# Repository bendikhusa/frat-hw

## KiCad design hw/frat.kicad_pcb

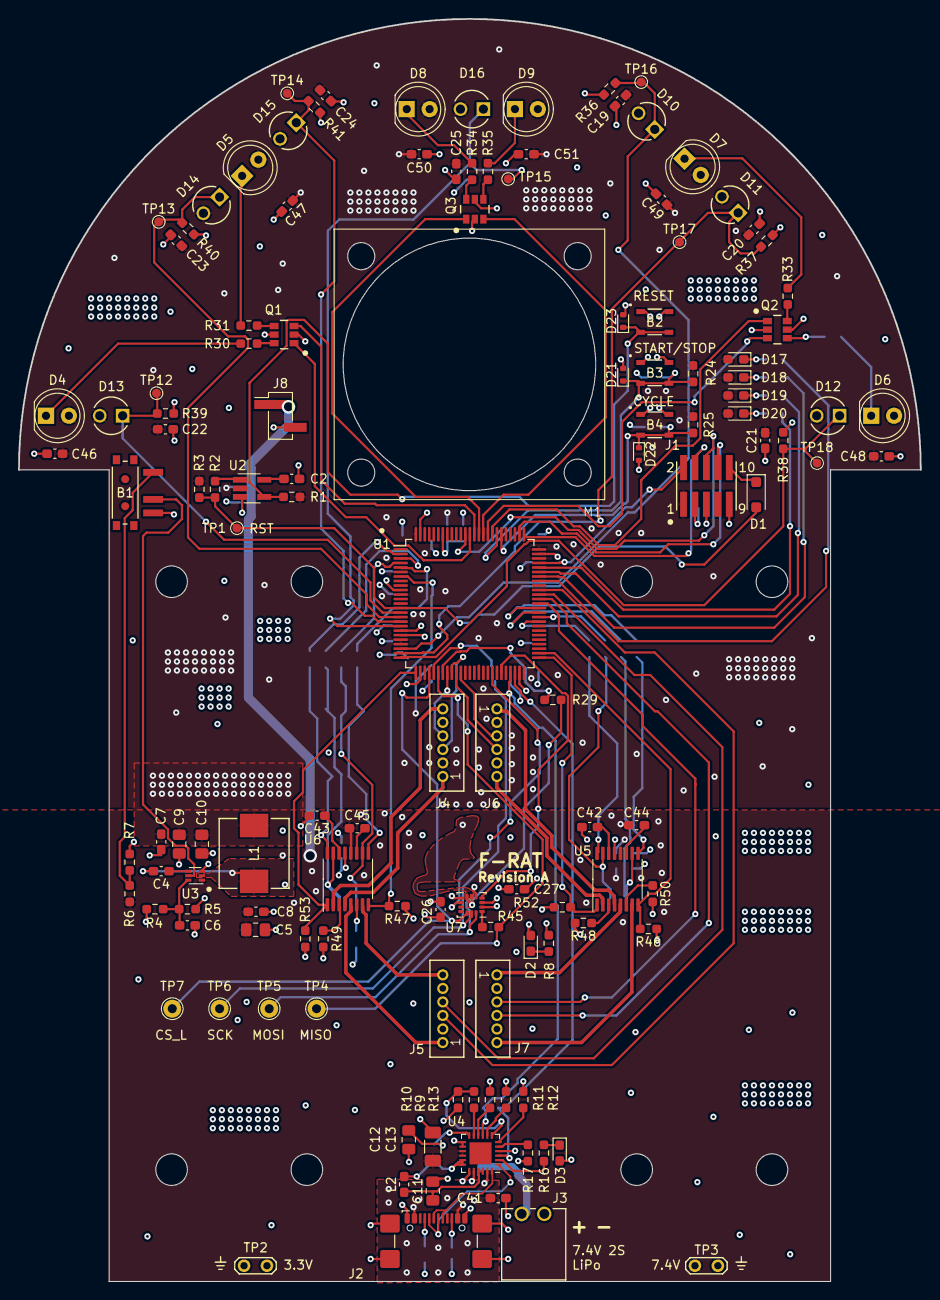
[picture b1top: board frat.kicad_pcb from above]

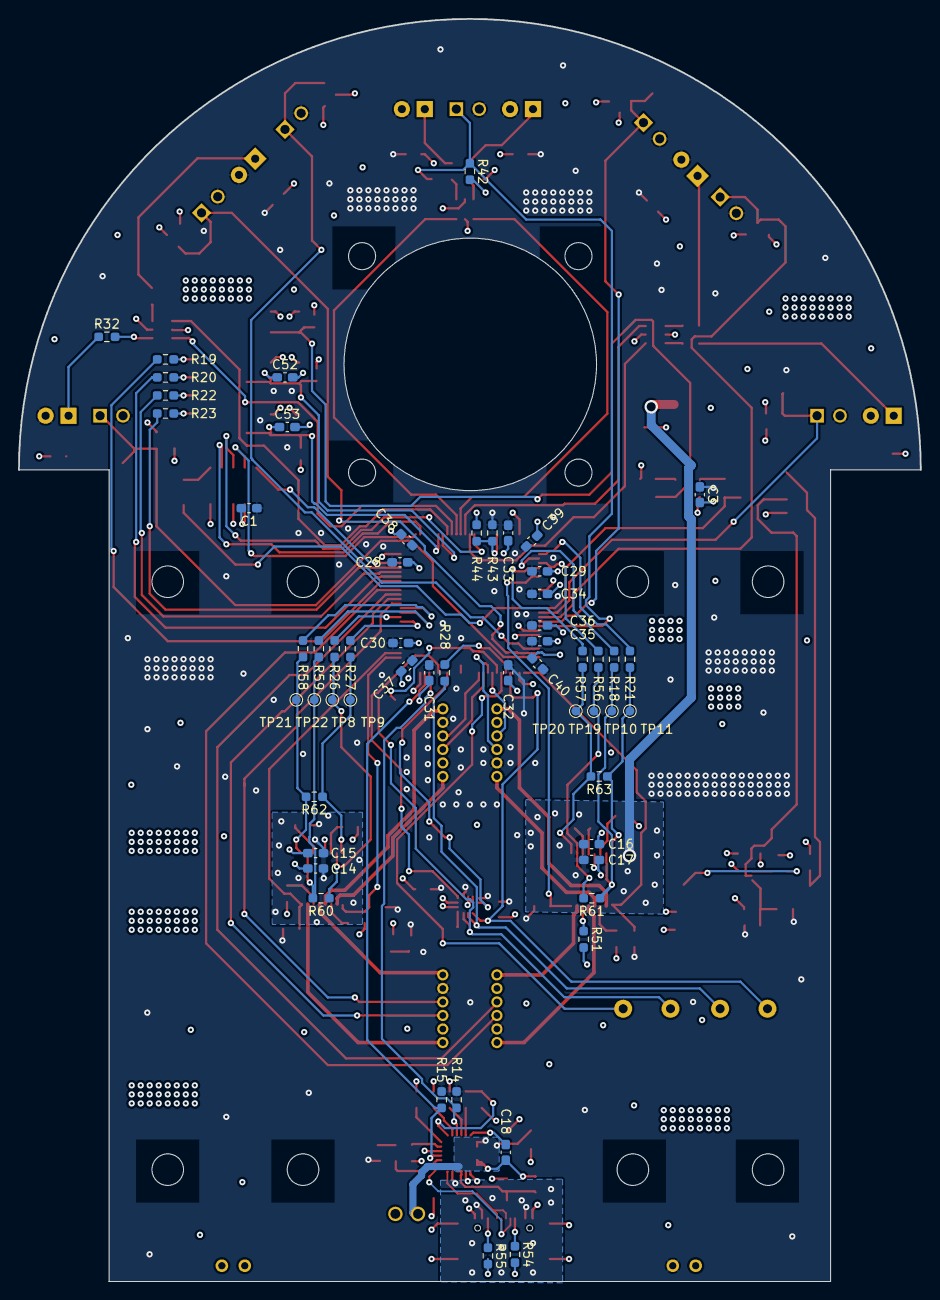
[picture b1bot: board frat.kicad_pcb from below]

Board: 4 copper layers, 100.0 x 140.0 mm, 188 parts (56 on the bottom side), 126 nets.

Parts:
B1: PCM12SMTR; PCM12SMTR_CNK
B2, B3, B4: PTS830GG140GSMTRLFS; PTS830GG140GSMTRLFS_CNK
C1, C2, C3, C4, C7, C8, C15, C17, C26, C27, C28, C29, C30, C31, C32, C33, C34, C35, C36, C41, C52, C53: 100 nF; C_0603_1608Metric_Pad1.08x0.95mm_HandSolder
C5, C9, C10, C11, C12: 10 uF; C_0805_2012Metric_Pad1.18x1.45mm_HandSolder
C6: 22 pF; C_0603_1608Metric_Pad1.08x0.95mm_HandSolder
C13: 47 uF; C_1206_3216Metric_Pad1.33x1.80mm_HandSolder
C14, C16, C37, C38, C39, C40: 10 uF; C_0603_1608Metric_Pad1.08x0.95mm_HandSolder
C18: 47 nF; C_0603_1608Metric_Pad1.08x0.95mm_HandSolder
C19, C20, C21, C22, C23, C24, C25, C42, C43: 2.2 uF; C_0603_1608Metric_Pad1.08x0.95mm_HandSolder
C44, C45: 10 nF; C_0603_1608Metric_Pad1.08x0.95mm_HandSolder
C46, C47, C48, C49, C50, C51: 4.7 uF; C_0603_1608Metric_Pad1.08x0.95mm_HandSolder
D1: PMEG2010AEH; D_SOD-123F
D2, D17, D18, D19, D20: HSMG-C190; LED_0603_1608Metric_Pad1.05x0.95mm_HandSolder
D3: HSMH-H190; LED_0603_1608Metric_Pad1.05x0.95mm_HandSolder
D4, D5, D6, D7, D8, D9: 950 nm, Vf = 1.5V typ; LED_D5.0mm_IRGrey
D10, D11, D12, D13, D14, D15, D16: LED_TEFT4300_VIS
D21, D22, D23: ESD5Z3.3T5G; D_SOD-523
J1: Conn_ARM_JTAG_SWD_10; CON10_2X5_DUK_FTSH_SAI
J2: USB_C_Receptacle_USB2.0; USB_C_Receptacle_GCT_USB4110
J3: 1778625; CONN_1814841
J4, J5, J6, J7: JST_B6B-ZR; CONN_B6B-ZR_JST
J8: Conn_01x02_Pin; PinHeader_1x02_P2.54mm_Vertical_SMD_Pin1Left
L1: 3.3 uH; IND_SRP7050_BRN
L2: 1 uH; L_0603_1608Metric_Pad1.05x0.95mm_HandSolder
M1: Fan; 30mm fan
M2, M3: N20 wheel assembly; N20
Q1, Q2, Q3: DMN2053UVT; TSOT-26-6
R1, R3, R5, R9, R10, R14, R15, R17, R24, R25, R43, R44, R46, R47, R52, R53: 10k; R_0603_1608Metric_Pad0.98x0.95mm_HandSolder
R2, R48, R49, R50, R51, R60, R61, R62, R63: 0; R_0603_1608Metric_Pad0.98x0.95mm_HandSolder
R4, R7: 30.9k; R_0603_1608Metric_Pad0.98x0.95mm_HandSolder
R6: 100k; R_0603_1608Metric_Pad0.98x0.95mm_HandSolder
R8, R19, R20, R22, R23: 300; R_0603_1608Metric_Pad0.98x0.95mm_HandSolder
R11: 330; R_0603_1608Metric_Pad0.98x0.95mm_HandSolder
R12: 150k; R_0603_1608Metric_Pad0.98x0.95mm_HandSolder
R13: 8.06k; R_0603_1608Metric_Pad0.98x0.95mm_HandSolder
R16: 430; R_0603_1608Metric_Pad0.98x0.95mm_HandSolder
R18, R21, R26, R27, R28, R29, R45, R56, R57, R58, R59: 33; R_0603_1608Metric_Pad0.98x0.95mm_HandSolder
R30, R31, R32, R33, R34, R35: 18; R_0603_1608Metric_Pad0.98x0.95mm_HandSolder
R36, R37, R38, R39, R40, R41, R42: 1.8k; R_0603_1608Metric_Pad0.98x0.95mm_HandSolder
R54, R55: 5.1k; R_0603_1608Metric_Pad0.98x0.95mm_HandSolder
TP1, TP8, TP9, TP10, TP11, TP12, TP13, TP14, TP15, TP16, TP17, TP18, TP19, TP20, TP21, TP22: TestPoint; TestPoint_Pad_D1.0mm
TP2, TP3: TestPoint_2Pole; TestPoint_2Pads_Pitch2.54mm_Drill0.8mm
TP4, TP5, TP6, TP7: TestPoint; TestPoint_THTPad_D2.0mm_Drill1.0mm
U1: STM32L562VET6; LQFP-100_14x14mm_P0.5mm
U2: TPS3840DL30DBV; SOT-23-5_HandSoldering
U3: TPS562202; SOT-563
U4: BQ25886RGET; VQFN-24-1EP_4x4mm_P0.5mm_EP2.45x2.45mm
U5, U6: DRV8833PW; TSSOP-16_4.4x5mm_P0.65mm
U7: LSM6DS3; LGA-14_3x2.5mm_P0.5mm_LayoutBorder3x4y

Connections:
+3.3V: C1.1, C3.1, C6.1, C7.1, C9.1, C10.1, C19.1, C20.1, C21.1, C22.1, C23.1, C24.1, C25.1, C26.1, C27.1, C28.1, C29.1, C30.1, C31.1, C32.1, C33.1, C34.1, C35.1, C36.1, C37.1, C38.1, C39.1, C40.1, C46.1, C47.1, C48.1, C49.1, C50.1, C51.1, D2.2, D3.2, D4.2, D5.2, D6.2, D7.2, D8.2, D9.2, D10.2 (A), D11.2 (A), D12.2 (A), D13.2 (A), D14.2 (A), D15.2 (A), D16.2 (A), D17.2, D18.2, D19.2, D20.2, J1.1 (VTref), J4.2 (VCC), J5.2 (VCC), J6.2 (VCC), J7.2 (VCC), L1.2, R1.1, R3.1, R4.1, R14.1, R15.1, R24.1, R25.1, R43.1, R46.1, R47.1, R52.1, R53.1, TP2.2, U1.6 (VBAT), U1.11 (VDD), U1.21 (VREF+), U1.22 (VDDA), U1.28 (VDD), U1.50 (VDD), U1.73 (VDDUSB), U1.75 (VDD), U1.100 (VDD), U2.2 (VDD), U7.5 (VDDIO), U7.8 (VDD)
+BATT: C5.1, C8.1, C13.1, C14.1, C15.1, C16.1, C17.1, C44.1, C45.1, J8.1, R6.2, TP3.2, U3.1 (VIN), U4.15 (SYS), U4.16 (SYS), U5.12 (VM), U6.12 (VM)
+BATT_DIRECT: C12.1, J3.1, U4.13 (BAT), U4.14 (BAT)
/Battery/CE_L: R15.2, U1.48 (PB11), U4.3 (~CE)
/Battery/PG_L: R14.2, U1.47 (PB10), U4.9 (~PG)
/Connectors/L1_MOTOR+: J6.6 (M1), U6.2 (AOUT1)
/Connectors/L1_MOTOR-: J6.1 (M2), U6.4 (AOUT2)
/Connectors/L1_MOTOR_C1: J6.4 (C1), U1.33 (PC4)
/Connectors/L1_MOTOR_C2: J6.3 (C2), U1.34 (PC5)
/Connectors/L2_MOTOR+: J7.6 (M1), U6.7 (BOUT1)
/Connectors/L2_MOTOR-: J7.1 (M2), U6.5 (BOUT2)
/Connectors/L2_MOTOR_C1: J7.4 (C1), U1.65 (PC8)
/Connectors/L2_MOTOR_C2: J7.3 (C2), U1.66 (PC9)
/Connectors/R1_MOTOR+: J4.6 (M1), U5.2 (AOUT1)
/Connectors/R1_MOTOR-: J4.1 (M2), U5.4 (AOUT2)
/Connectors/R1_MOTOR_C1: J4.4 (C1), U1.35 (PB0)
/Connectors/R1_MOTOR_C2: J4.3 (C2), U1.36 (PB1)
/Connectors/R2_MOTOR+: J5.6 (M1), U5.7 (BOUT1)
/Connectors/R2_MOTOR-: J5.1 (M2), U5.5 (BOUT2)
/Connectors/R2_MOTOR_C1: J5.4 (C1), U1.64 (PC7)
/Connectors/R2_MOTOR_C2: J5.3 (C2), U1.63 (PC6)
/MCU/BOOT_MODE: R43.2, R44.1, U1.94 (PH3/BOOT0)
/MCU/CYCLE_PROGRAM_BUTTON: B4.3 (A), B4.4 (C), C53.1, D22.1 (K), R25.2, U1.81 (PD0)
/MCU/LED0: R19.2, U1.68 (PA9)
/MCU/LED1: R20.2, U1.69 (PA10)
/MCU/LED2: R22.2, U1.70 (PA11)
/MCU/LED3: R23.2, U1.71 (PA12)
/MCU/LF_DETECTOR: D13.1 (K), R39.1, TP12.1, U1.15 (PC0)
/MCU/LF_EMITTER: Q1.1 (G2), U1.88 (PD7)
/MCU/L_DETECTOR1: D14.1 (K), R40.1, TP13.1, U1.16 (PC1)
/MCU/L_DETECTOR2: D15.1 (K), R41.1, TP14.1, U1.17 (PC2)
/MCU/L_EMITTER: Q1.3 (G2), U1.87 (PD6)
/MCU/L_MOTOR_FAULT_L: R47.2, U1.7 (PC13), U6.8 (nFAULT)
/MCU/L_MOTOR_SLEEP_L: R53.2, U1.26 (PA3), U6.1 (nSLEEP)
/MCU/MCU_RST_L: D1.2 (A), R2.2, R3.2, TP1.1, U1.14 (NRST)
/MCU/MCU_SWDCLK_TCK: J1.4 (SWDCLK/TCK), U1.76 (PA14/TCK/SWCLK)
/MCU/MCU_SWDIO_TMS: J1.2 (SWDIO/TMS), U1.72 (PA13/TMS/SWDIO)
/MCU/MCU_SWO_TDO: J1.6 (SWO/TDO), U1.89 (PB3/TDO/SWO)
/MCU/MCU_TDI: J1.8 (NC/TDI), U1.77 (PA15/TDI)
/MCU/MF_DETECTOR: D16.1 (K), R42.1, TP15.1, U1.18 (PC3)
/MCU/MF_EMITTER_1: Q3.1 (G2), U1.86 (PD5)
/MCU/MF_EMITTER_2: Q3.3 (G2), U1.85 (PD4)
/MCU/MOTOR_L_APWM1: R21.2, R63.1, TP11.1, U6.16 (AIN1)
/MCU/MOTOR_L_APWM2: R57.2, R63.2, TP20.1, U6.9 (BIN1)
/MCU/MOTOR_L_BPWM1: R18.2, R61.1, TP10.1, U6.15 (AIN2)
/MCU/MOTOR_L_BPWM2: R56.2, R61.2, TP19.1, U6.10 (BIN2)
/MCU/MOTOR_R_APWM1: R27.2, R62.1, TP9.1, U5.16 (AIN1)
/MCU/MOTOR_R_APWM2: R58.2, R62.2, TP21.1, U5.9 (BIN1)
/MCU/MOTOR_R_BPWM1: R26.2, R60.1, TP8.1, U5.15 (AIN2)
/MCU/MOTOR_R_BPWM2: R59.2, R60.2, TP22.1, U5.10 (BIN2)
/MCU/RF_DETECTOR: D12.1 (K), R38.1, TP18.1, U1.25 (PA2)
/MCU/RF_EMITTER: Q2.1 (G2), U1.83 (PD2)
/MCU/R_DETECTOR1: D11.1 (K), R37.1, TP17.1, U1.24 (PA1)
/MCU/R_DETECTOR2: D10.1 (K), R36.1, TP16.1, U1.23 (PA0)
/MCU/R_EMITTER: Q2.3 (G2), U1.84 (PD3)
/MCU/R_MOTOR_FAULT_L: R46.2, U1.52 (PB13), U5.8 (nFAULT)
/MCU/R_MOTOR_SLEEP_L: R52.2, U1.51 (PB12), U5.1 (nSLEEP)
/MCU/SPI_CS_L: TP7.1, U1.29 (PA4), U7.12 (CS)
/MCU/SPI_INT1: U1.45 (PE14), U7.4 (INT1)
/MCU/SPI_INT2: U1.43 (PE12), U7.9 (INT2)
/MCU/SPI_MISO: R45.1, TP4.1, U1.31 (PA6)
/MCU/SPI_MOSI: R29.2, TP5.1, U7.14 (SDA)
/MCU/SPI_SCK: R28.2, TP6.1, U7.13 (SCL)
/MCU/START_STOP_BUTTON: B3.3 (A), B3.4 (C), C52.1, D21.1 (K), R24.2, U1.82 (PD1)
/MCU/SWD_RST_L: D1.1 (K), J1.10 (~RESET)
/Power/DCDC_EN: B1.2 (B), U3.5 (EN)
/USB_D+: J2.A6 (D+), J2.B6 (D+), U4.24 (D+)
/USB_D-: J2.A7 (D-), J2.B7 (D-), U4.1 (D-)
GND: B1.3 (C), B2.1 (B), B2.2 (D), B3.1 (B), B3.2 (D), B4.1 (B), B4.2 (D), C1.2, C2.2, C3.2, C5.2, C7.2, C8.2, C9.2, C10.2, C11.2, C12.2, C13.2, C14.2, C15.2, C16.2, C17.2, C19.2, C20.2, C21.2, C22.2, C23.2, C24.2, C25.2, C26.2, C27.2, C28.2, C29.2, C30.2, C31.2, C32.2, C33.2, C34.2, C35.2, C36.2, C37.2, C38.2, C39.2, C40.2, C41.2, C42.2, C43.2, C46.2, C47.2, C48.2, C49.2, C50.2, C51.2, C52.2, C53.2, D21.2 (A), D22.2 (A), D23.2 (A), J1.3 (GND), J1.5 (GND), J1.9 (GNDDetect), J2.A1 (GND), J2.A12 (GND), J2.B1 (GND), J2.B12 (GND), J2.S1 (SHIELD), J3.2, J4.5 (GND), J5.5 (GND), J6.5 (GND), J7.5 (GND), J8.2, Q1.2 (S2), Q1.5 (S2), Q2.2 (S2), Q2.5 (S2), Q3.2 (S2), Q3.5 (S2), R5.2, R7.2, R8.2, R10.2, R11.2, R12.2, R13.2, R17.2, R36.2, R37.2, R38.2, R39.2, R40.2, R41.2, R42.2, R44.2, R48.2, R49.2, R50.2, R51.2, R54.2, R55.2, TP2.1, TP3.1, U1.10 (VSS), U1.19 (VSSA), U1.20 (VREF-), U1.27 (VSS), U1.49 (VSS), U1.74 (VSS), U1.99 (VSS), U2.3 (GND), U3.3 (GND), U4.4 (GND), U4.19 (GND), U4.20 (GND), U5.13 (GND), U6.13 (GND), U7.2 (SDX), U7.3 (SCX), U7.6 (GND), U7.7 (GND)
unnamed: B1.1 (A), R6.1, R7.1
unnamed: B2.3 (A), B2.4 (C), D23.1 (K), R1.2, U2.4 (~MR/NC)
unnamed: C11.1, L2.1, U4.21 (PMID), U4.22 (PMID)
unnamed: C18.1, L2.2, U4.17 (SW), U4.18 (SW)
unnamed: D2.1, R8.1
unnamed: D3.1, R16.1
unnamed: D4.1, R30.1
unnamed: D5.1, R31.1
unnamed: D6.1, R32.1
unnamed: D7.1, R33.1
unnamed: D8.1, R34.1
unnamed: D9.1, R35.1
unnamed: D17.1, R19.1
unnamed: D18.1, R20.1
unnamed: D19.1, R22.1
unnamed: D20.1, R23.1
unnamed: J2.A5 (CC1), R54.1
unnamed: J2.B5 (CC2), R55.1
unnamed: Q1.6 (D2), R30.2
unnamed: Q1.4 (D2), R31.2
unnamed: Q2.6 (D2), R33.2
unnamed: Q2.4 (D2), R32.2
unnamed: Q3.6 (D2), R34.2
unnamed: Q3.4 (D2), R35.2
unnamed: R28.1, U1.30 (PA5)
unnamed: R29.1, U1.32 (PA7)
unnamed: R27.1, U1.59 (PD12)
unnamed: R26.1, U1.60 (PD13)
unnamed: R59.1, U1.61 (PD14)
unnamed: R58.1, U1.62 (PD15)
unnamed: R21.1, U1.2 (PE3)
unnamed: R18.1, U1.3 (PE4)
unnamed: R56.1, U1.4 (PE5)
unnamed: R57.1, U1.5 (PE6)
unnamed: C2.1, U2.5 (CT)
unnamed: R2.1, U2.1 (~RESET)
unnamed: C4.1, U3.4 (BST)
unnamed: C6.2, R4.2, R5.1, U3.6 (FB)
unnamed: C4.2, L1.1, U3.2 (SW)
unnamed: C18.2, U4.12 (BTST)
unnamed: R13.1, U4.10 (ICHGSET)
unnamed: R11.1, U4.8 (ILIM)
unnamed: R17.1, U4.5 (OTG)
unnamed: R9.1, U4.11 (REGN)
unnamed: R16.2, U4.2 (STAT)
unnamed: R9.2, R10.1, U4.7 (TS)
unnamed: R12.1, U4.6 (VSET)
unnamed: R48.1, U5.3 (AISEN)
unnamed: R50.1, U5.6 (BISEN)
unnamed: C44.2, U5.11 (VCP)
unnamed: C42.1, U5.14 (VINT)
unnamed: R49.1, U6.3 (AISEN)
unnamed: R51.1, U6.6 (BISEN)
unnamed: C45.2, U6.11 (VCP)
unnamed: C43.1, U6.14 (VINT)
unnamed: R45.2, U7.1 (SDO/SA0)
VBUS: C41.1, J2.A4 (VBUS), J2.A9 (VBUS), J2.B4 (VBUS), J2.B9 (VBUS), U4.23 (VBUS)

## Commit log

2023-12-11 Added HW project - Added schematic files - Added PCB file - Added symbols and footprints - Added production files - Defined folder structure for mechanical files
2023-12-11 Removed kicad generated files - Removed footprint and symbol lib table - Removed backup folder - Removed PRL file - Added kicad generated files to gitignore
2023-12-12 Add step files and Fusion 360 project for mechanical design
2023-12-12 Revert "Add step files and Fusion 360 project for mechanical design"
    This reverts commit e2e2db65c93b147c40e331ae3ebf91e184aca930.
2024-01-06 Fixed reference designators being wrong for hierarchical clones
    Moving PCB and schematic files to separate folders caused reference designators to become cloned for right and left motor drivers, revert this change
